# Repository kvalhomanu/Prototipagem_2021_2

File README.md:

# Prototipagem_2021_2
Repositório para a disciplina de Prototipagem

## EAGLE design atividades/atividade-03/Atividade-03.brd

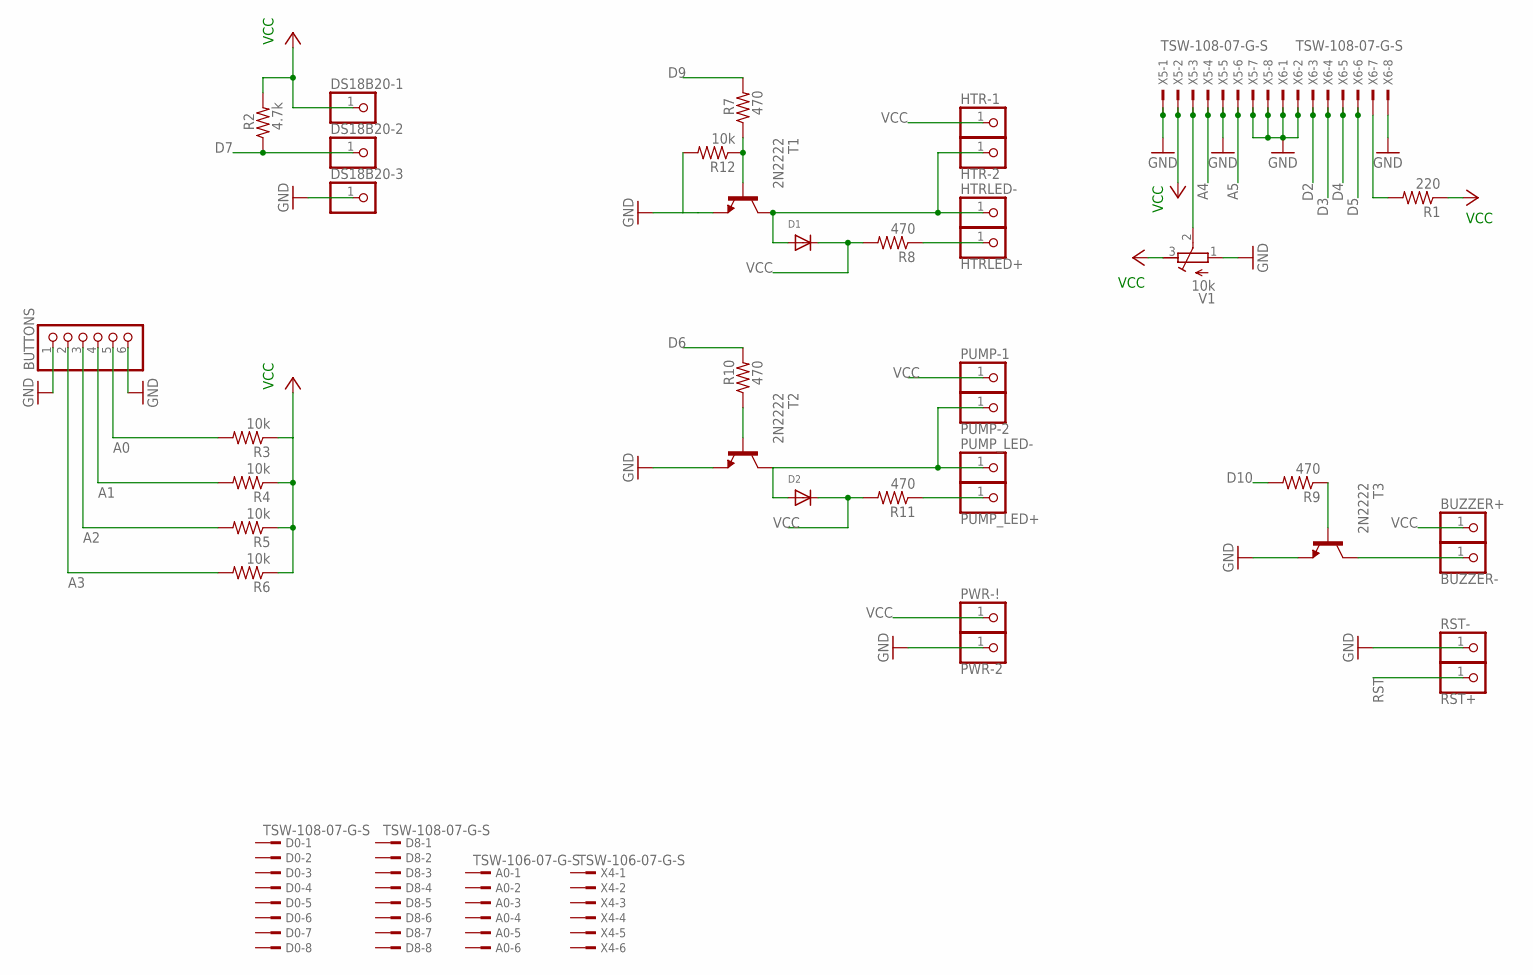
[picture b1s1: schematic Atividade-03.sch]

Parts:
A0: TSW-106-07-G-S; TSW-106-XX-G-S
BUTTONS: PINHD-1X6; 1X06
BUZZER+: PINHD-1X1; 1X01
BUZZER-: PINHD-1X1; 1X01
D0, D8: TSW-108-07-G-S; TSW-108-XX-G-S
D1, D2: DIODEDO-1N4148; DO-1N4148
DS18B20-1, DS18B20-2, DS18B20-3: PINHD-1X1; 1X01
HTR-1, HTR-2: PINHD-1X1; 1X01
HTRLED+: PINHD-1X1; 1X01
HTRLED-: PINHD-1X1; 1X01
PUMP-1, PUMP-2: PINHD-1X1; 1X01
PUMP_LED+: PINHD-1X1; 1X01
PUMP_LED-: PINHD-1X1; 1X01
PWR-2: PINHD-1X1; 1X01
PWR-!: PINHD-1X1; 1X01
R1: 220; 0207/7
R2: 4.7k; 0207/7
R3, R4, R5, R6, R12: 10k; 0207/7
R7, R8, R9, R10, R11: 470; 0207/7
RST+: PINHD-1X1; 1X01
RST-: PINHD-1X1; 1X01
T1, T2, T3: 2N2222; TO92-EBC-OVAL
V1: 10k; RTRIM5W
X4: TSW-106-07-G-S; TSW-106-XX-G-S
X5, X6: TSW-108-07-G-S; TSW-108-XX-G-S

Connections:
A0: BUTTONS.5, R3.2
A1: BUTTONS.4, R4.2
A2: BUTTONS.3, R5.2
A3: BUTTONS.2, R6.2
A4: X5.4
A5: X5.6
D2: X6.3
D3: X6.4
D4: X6.5
D5: X6.6
D6: R10.2
D7: DS18B20-2.1, R2.1
D9: R7.2
D10: R9.2
GND: BUTTONS.1, BUTTONS.6, DS18B20-3.1, PWR-2.1, R12.2, RST-.1, T1.E, T2.E, T3.E, V1.1 (A), X5.1, X5.5, X5.7, X5.8, X6.1, X6.2, X6.8
unnamed: V1.2 (S), X5.3
unnamed: R7.1, R12.1, T1.B
unnamed: D1.A, D2.A, HTR-2.1, HTRLED-.1, PUMP-2.1, PUMP_LED-.1, T1.C, T2.C
unnamed: R10.1, T2.B
unnamed: HTRLED+.1, PUMP_LED+.1, R8.1, R11.1
unnamed: R9.1, T3.B
unnamed: BUZZER-.1, T3.C
unnamed: R1.2, X6.7
RST: RST+.1
VCC: BUZZER+.1, D1.C, D2.C, DS18B20-1.1, HTR-1.1, PUMP-1.1, PWR-!.1, R1.1, R2.2, R3.1, R4.1, R5.1, R6.1, R8.2, R11.2, V1.3 (E), X5.2

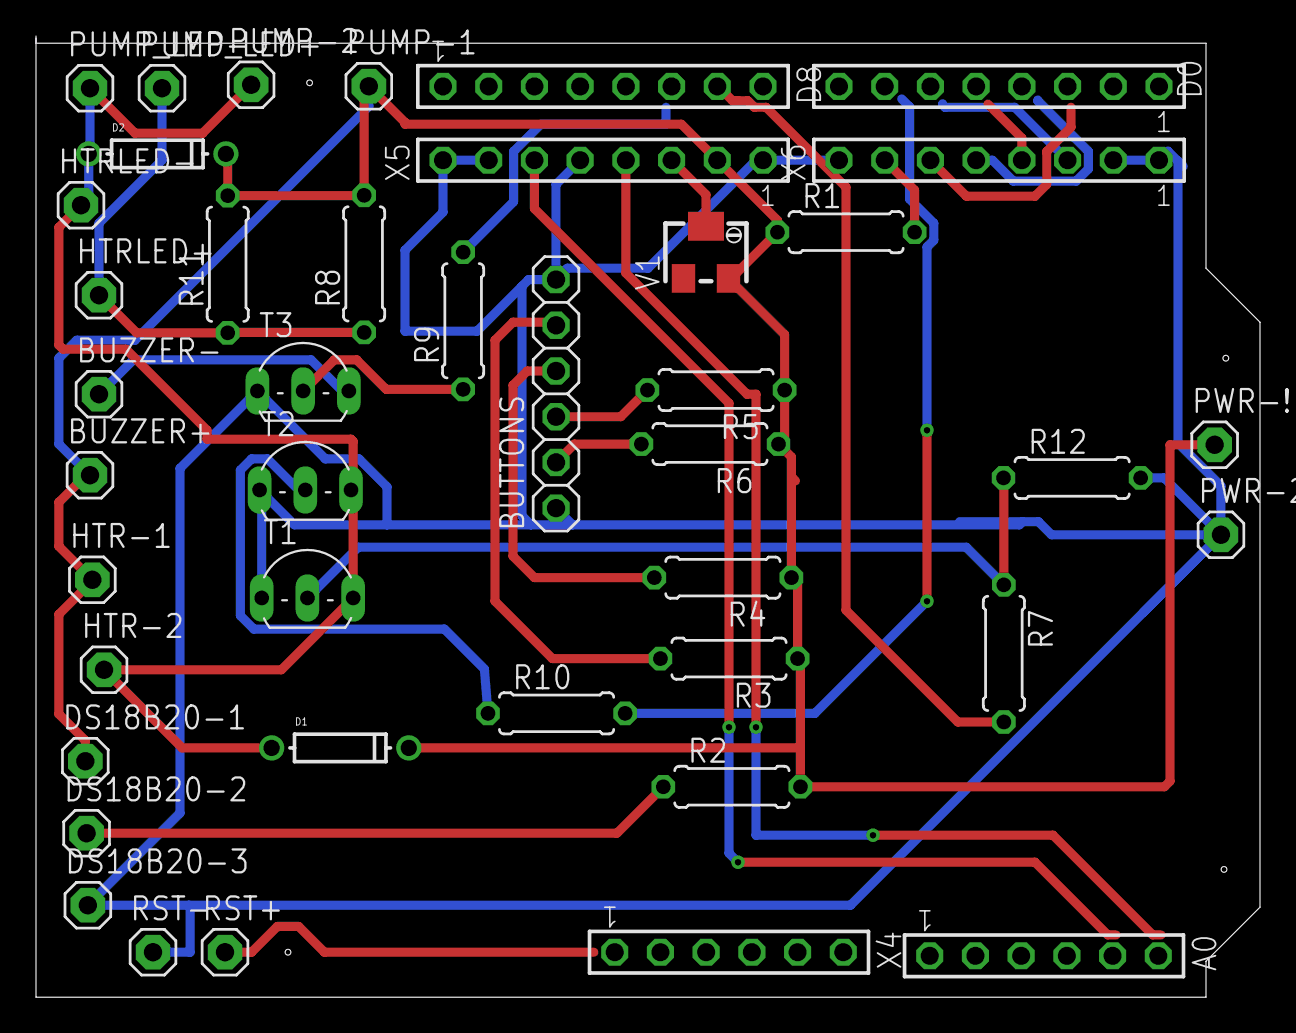
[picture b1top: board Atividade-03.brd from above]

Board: 2 copper layers, 68.0 x 53.4 mm, 42 parts (0 on the bottom side), 15 nets.

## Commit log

2021-12-04 Create Dummy_load
2022-03-19 Create text
2022-03-27 Create Link
